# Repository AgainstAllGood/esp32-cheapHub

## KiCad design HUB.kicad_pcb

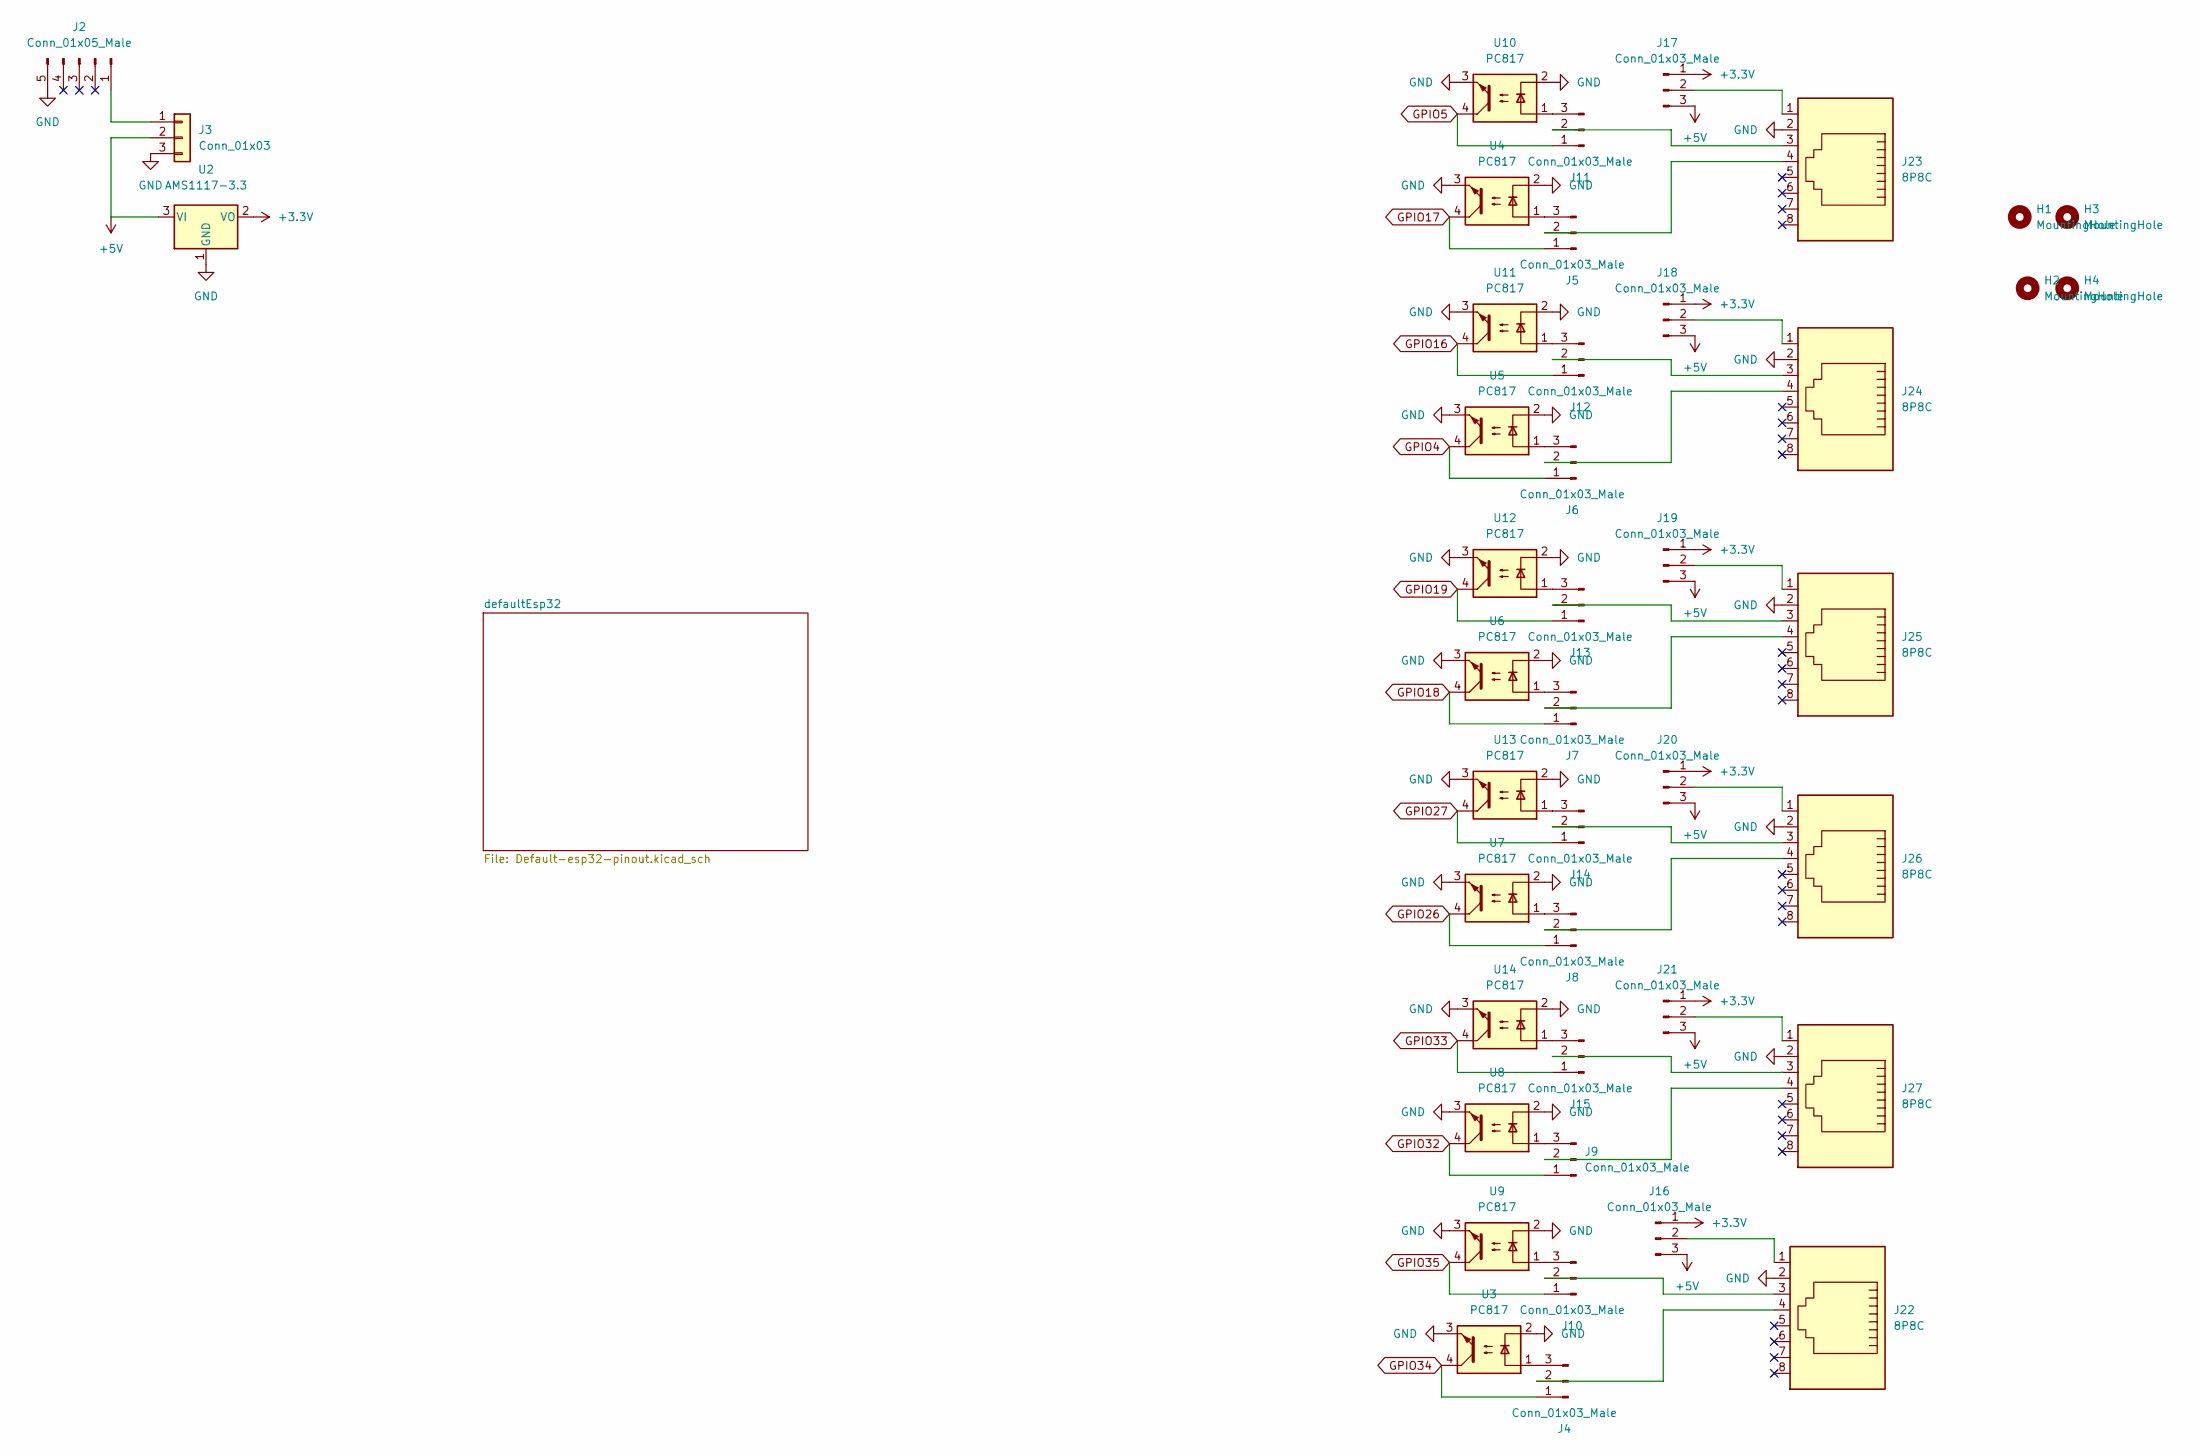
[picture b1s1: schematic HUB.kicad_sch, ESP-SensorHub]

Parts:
H1, H2, H3, H4: MountingHole; MountingHole_4.3mm_M4
J2: Conn_01x05_Male; PinSocket_1x05_P2.54mm_Vertical
J3: Conn_01x03; PinSocket_1x03_P2.54mm_Vertical
J4, J5, J6, J7, J8, J9, J10, J11, J12, J13, J14, J15, J16, J17, J18, J19, J20, J21: Conn_01x03_Male; PinHeader_1x03_P2.54mm_Vertical
J22, J23, J24, J25, J26, J27: 8P8C; RJ45_OST_PJ012-8P8CX_Vertical
U2: AMS1117-3.3; SOT-223-3_TabPin2
U3, U4, U5, U6, U7, U8, U9, U10, U11, U12, U13, U14: PC817; DIP-4_W7.62mm

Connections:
+3V3: J16.1, J17.1, J18.1, J19.1, J20.1, J21.1, U2.2 (VO); also elsewhere on the board
+5V: J3.2, J16.3, J17.3, J18.3, J19.3, J20.3, J21.3, U2.3 (VI)
GND: J2.5, J3.3, J22.2, J23.2, J24.2, J25.2, J26.2, J27.2, U2.1 (GND), U3.2, U3.3, U4.2, U4.3, U5.2, U5.3, U6.2, U6.3, U7.2, U7.3, U8.2, U8.3, U9.2, U9.3, U10.2, U10.3, U11.2, U11.3, U12.2, U12.3, U13.2, U13.3, U14.2, U14.3; also elsewhere on the board
GPIO4: J6.1, U5.4; also elsewhere on the board
GPIO5: J11.1, U10.4; also elsewhere on the board
GPIO16: J12.1, U11.4; also elsewhere on the board
GPIO17: J5.1, U4.4; also elsewhere on the board
GPIO18: J7.1, U6.4; also elsewhere on the board
GPIO19: J13.1, U12.4; also elsewhere on the board
GPIO26: J8.1, U7.4; also elsewhere on the board
GPIO27: J14.1, U13.4; also elsewhere on the board
GPIO32: J9.1, U8.4; also elsewhere on the board
GPIO33: J15.1, U14.4; also elsewhere on the board
GPIO34: J4.1, U3.4; also elsewhere on the board
GPIO35: J10.1, U9.4; also elsewhere on the board
unnamed: J2.1, J3.1
unnamed: J4.3, U3.1
unnamed: J5.3, U4.1
unnamed: J6.3, U5.1
unnamed: J7.3, U6.1
unnamed: J8.3, U7.1
unnamed: J9.3, U8.1
unnamed: J10.2, J22.3
unnamed: J10.3, U9.1
unnamed: J11.2, J23.3
unnamed: J11.3, U10.1
unnamed: J12.2, J24.3
unnamed: J12.3, U11.1
unnamed: J13.2, J25.3
unnamed: J13.3, U12.1
unnamed: J14.2, J26.3
unnamed: J14.3, U13.1
unnamed: J15.2, J27.3
unnamed: J15.3, U14.1
unnamed: J16.2, J22.1
unnamed: J17.2, J23.1
unnamed: J18.2, J24.1
unnamed: J19.2, J25.1
unnamed: J20.2, J26.1
unnamed: J21.2, J27.1
unnamed: J4.2, J22.4
unnamed: J5.2, J23.4
unnamed: J6.2, J24.4
unnamed: J7.2, J25.4
unnamed: J8.2, J26.4
unnamed: J9.2, J27.4

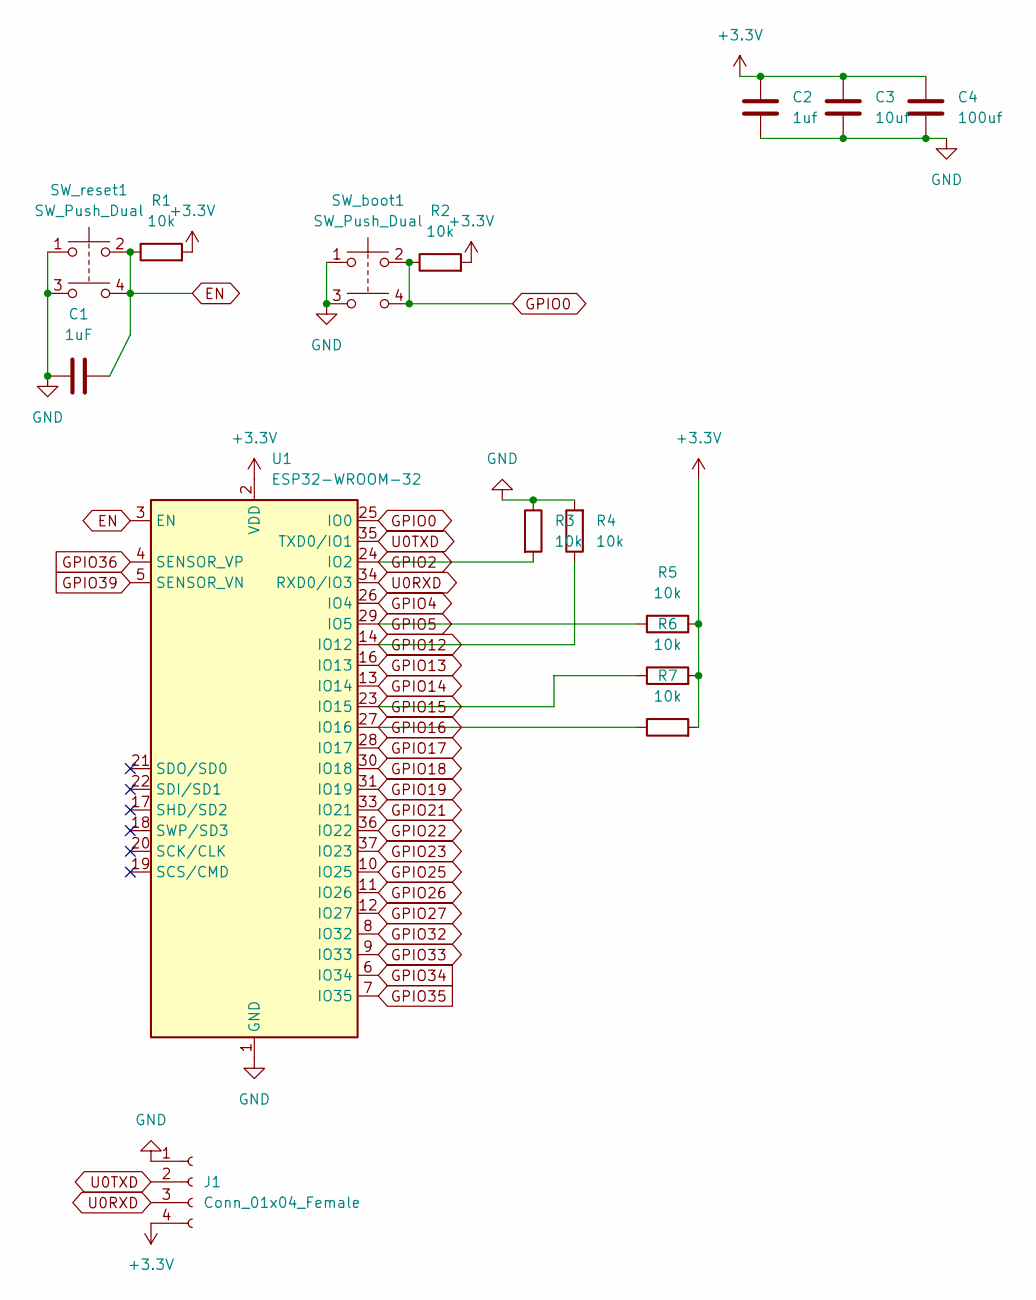
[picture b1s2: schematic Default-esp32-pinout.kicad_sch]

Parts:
C1: 1uF; C_0402_1005Metric_Pad0.74x0.62mm_HandSolder
C2: 1uf; C_0402_1005Metric_Pad0.74x0.62mm_HandSolder
C3: 10uf; C_0402_1005Metric_Pad0.74x0.62mm_HandSolder
C4: 100uf; C_0402_1005Metric_Pad0.74x0.62mm_HandSolder
J1: Conn_01x04_Female; PinSocket_1x04_P2.54mm_Vertical
R1, R2, R3, R4, R5, R6, R7: 10k; R_0402_1005Metric_Pad0.72x0.64mm_HandSolder
SW_boot1: SW_Push_Dual; SW_PUSH_6mm_H4.3mm
SW_reset1: SW_Push_Dual; SW_PUSH_6mm_H4.3mm
U1: ESP32-WROOM-32

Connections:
+3V3: C2.1, C3.1, C4.1, J1.4, R1.2, R2.2, R5.2, R6.2, R7.2, U1.2 (VDD); also elsewhere on the board
EN: C1.2, R1.1, SW_reset1.2, SW_reset1.4, U1.3 (EN)
GND: C1.1, C2.2, C3.2, C4.2, J1.1, R3.1, R4.2, SW_boot1.1, SW_boot1.3, SW_reset1.1, SW_reset1.3, U1.1 (GND), U1.15 (GND), U1.38 (GND), U1.39 (GND); also elsewhere on the board
GPIO0: R2.1, SW_boot1.2, SW_boot1.4, U1.25 (IO0)
GPIO2: R3.2, U1.24 (IO2)
GPIO4: U1.26 (IO4); also elsewhere on the board
GPIO5: R5.1, U1.29 (IO5); also elsewhere on the board
GPIO12: R4.1, U1.14 (IO12)
GPIO13: U1.16 (IO13)
GPIO14: U1.13 (IO14)
GPIO15: R6.1, U1.23 (IO15)
GPIO16: R7.1, U1.27 (IO16); also elsewhere on the board
GPIO17: U1.28 (IO17); also elsewhere on the board
GPIO18: U1.30 (IO18); also elsewhere on the board
GPIO19: U1.31 (IO19); also elsewhere on the board
GPIO21: U1.33 (IO21)
GPIO22: U1.36 (IO22)
GPIO23: U1.37 (IO23)
GPIO25: U1.10 (IO25)
GPIO26: U1.11 (IO26); also elsewhere on the board
GPIO27: U1.12 (IO27); also elsewhere on the board
GPIO32: U1.8 (IO32); also elsewhere on the board
GPIO33: U1.9 (IO33); also elsewhere on the board
GPIO34: U1.6 (IO34); also elsewhere on the board
GPIO35: U1.7 (IO35); also elsewhere on the board
GPIO36: U1.4 (SENSOR_VP)
GPIO39: U1.5 (SENSOR_VN)
U0RXD: J1.3, U1.34 (RXD0/IO3)
U0TXD: J1.2, U1.35 (TXD0/IO1)

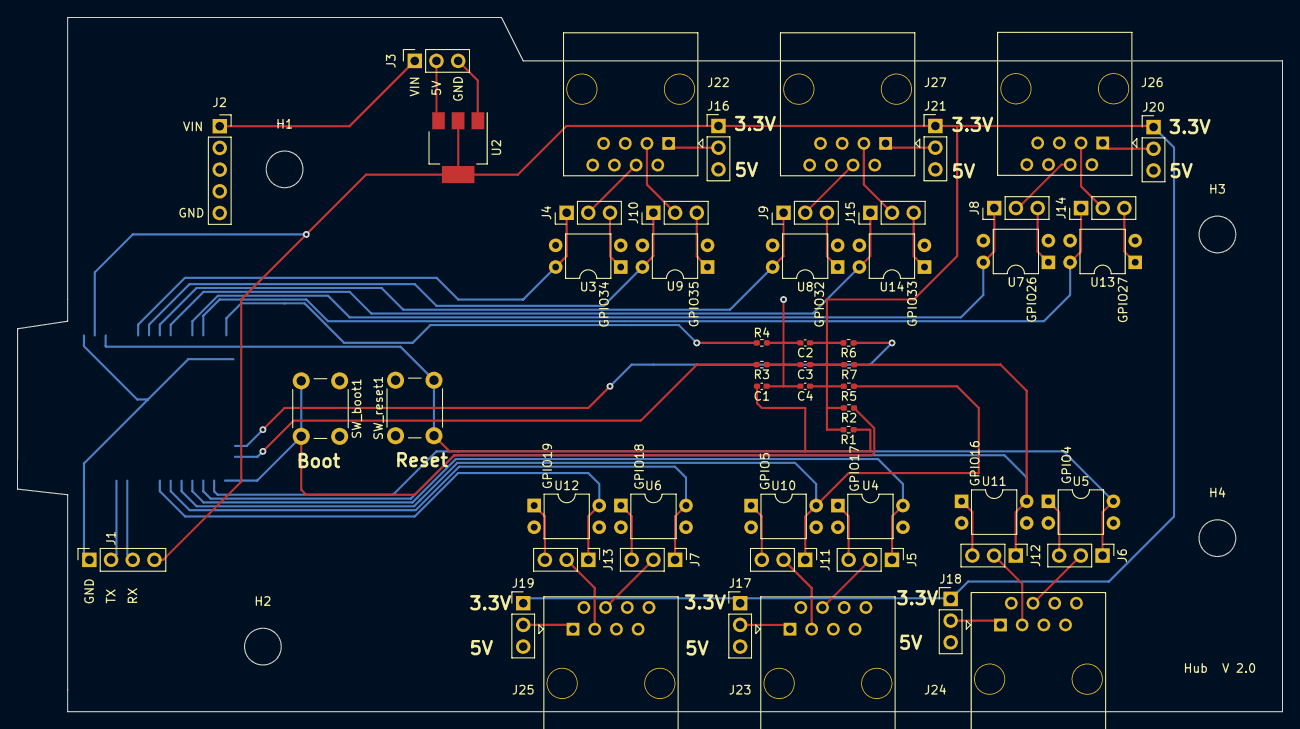
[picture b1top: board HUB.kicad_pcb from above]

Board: 4 copper layers, 148.1 x 81.3 mm, 58 parts (1 on the bottom side), 53 nets.
